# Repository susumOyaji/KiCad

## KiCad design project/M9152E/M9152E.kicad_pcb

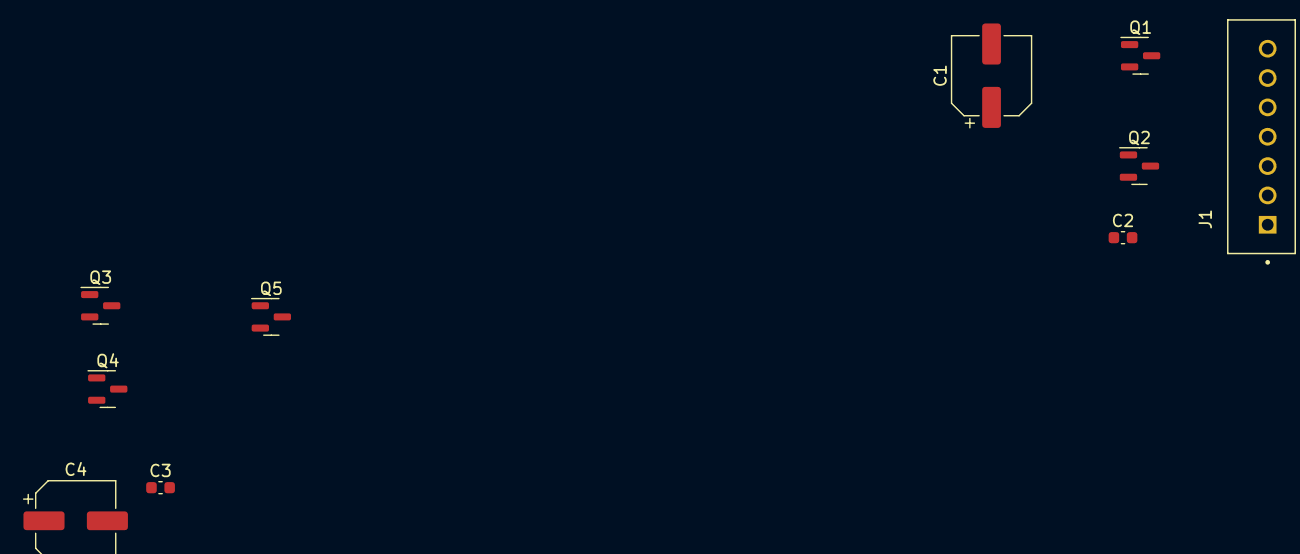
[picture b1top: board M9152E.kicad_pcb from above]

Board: 2 copper layers, 10 parts (0 on the bottom side), 8 nets, no tracks yet.

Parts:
C1, C4: C_Polarized_US; CP_Elec_6.3x5.4_Nichicon
C2, C3: 102; C_0603_1608Metric
J1: B7B-XH-A(LF)(SN); JST_B7B-XH-A(LF)(SN)
Q1, Q3: 2SC1815; SOT-23
Q2, Q4, Q5: 2SA1015; SOT-23

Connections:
GND: C2.2, Q2.2 (C), Q4.2 (C)
unnamed: C1.1, J1.5
unnamed: C1.2, Q1.1 (E), Q2.1 (E)
unnamed: C4.1, J1.4
unnamed: J1.7, Q1.2 (C), Q3.2 (C)
unnamed: Q1.3 (B), Q2.3 (B)
unnamed: C4.2, Q3.1 (E), Q4.1 (E)
unnamed: Q3.3 (B), Q4.3 (B)

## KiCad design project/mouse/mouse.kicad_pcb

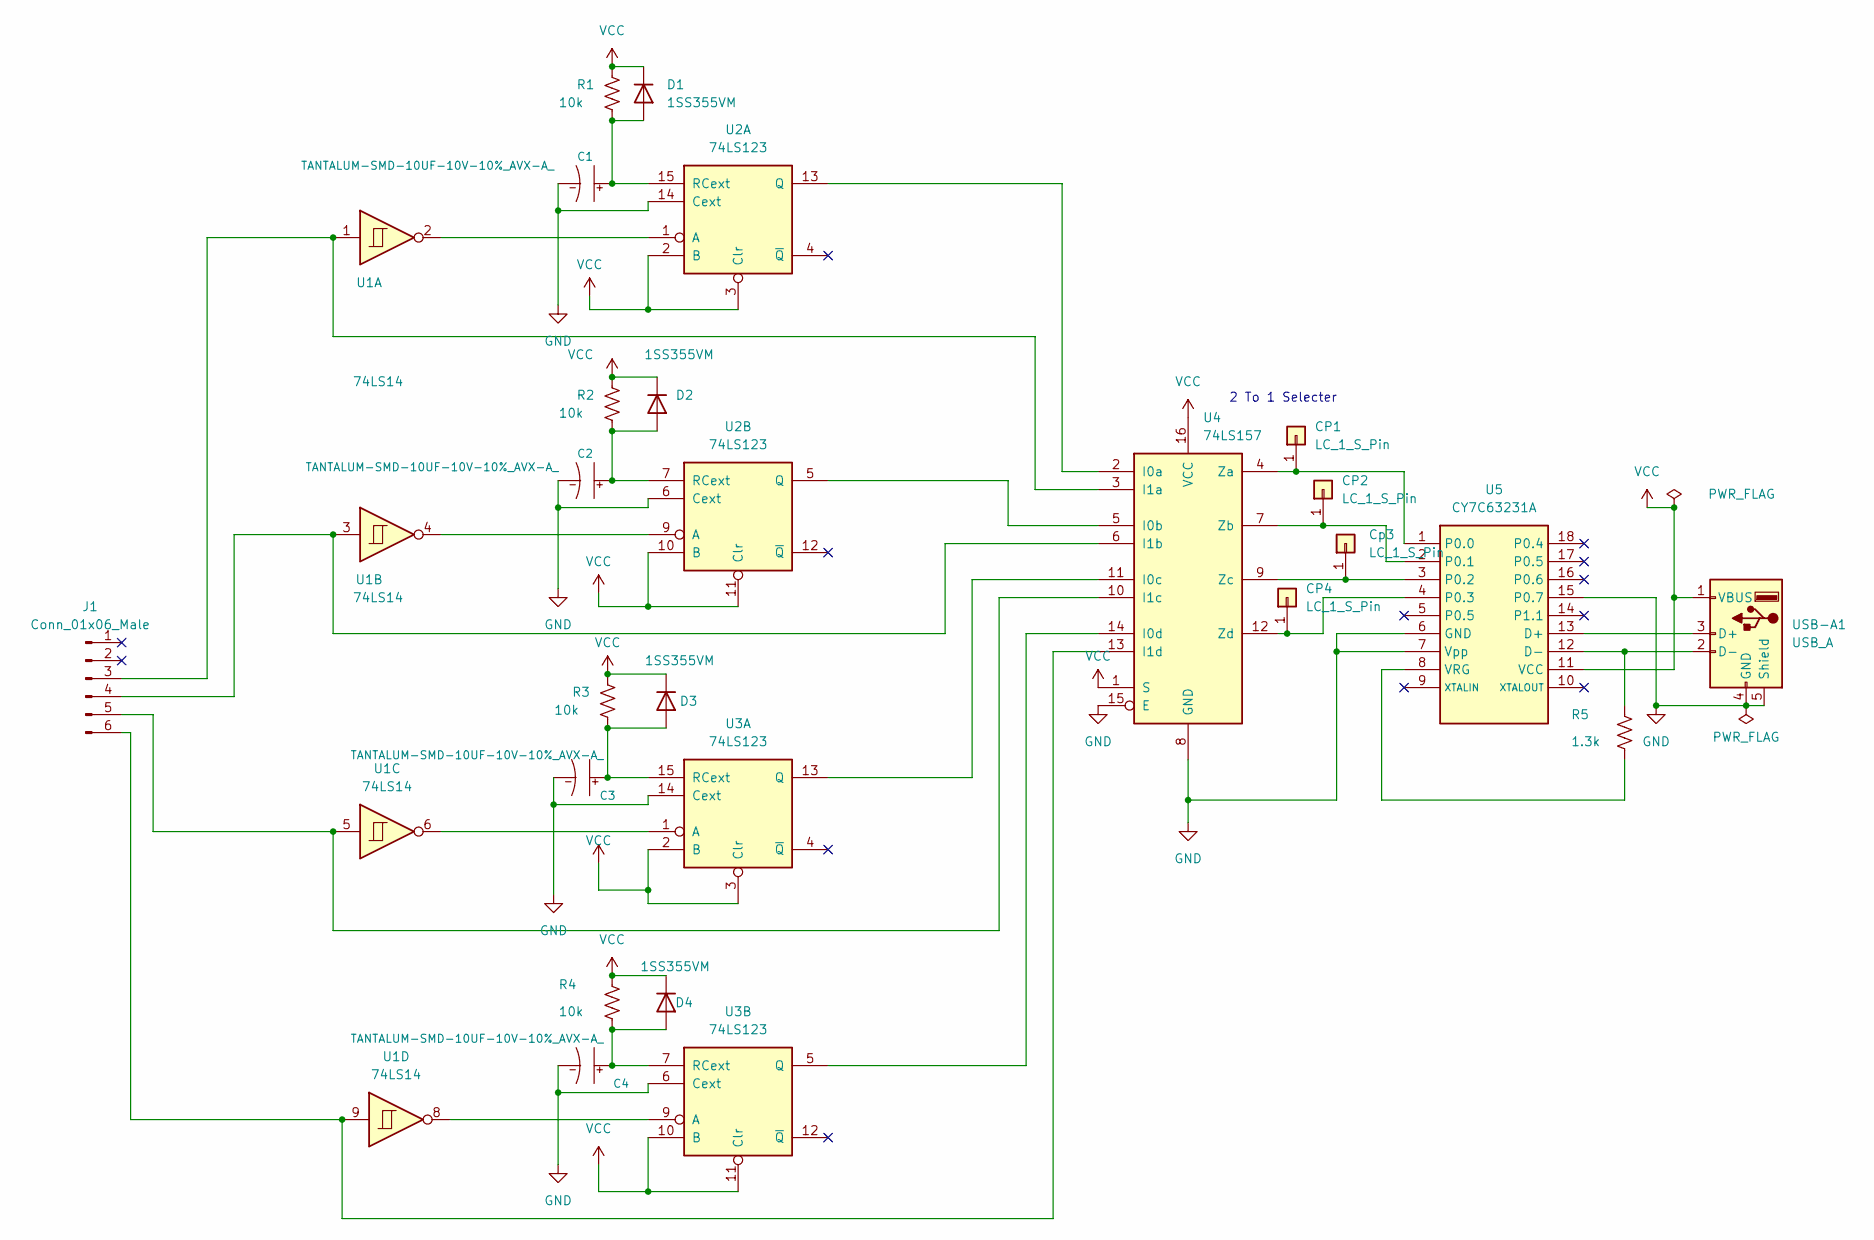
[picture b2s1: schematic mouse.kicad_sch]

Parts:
C1, C2, C3, C4: TANTALUM-SMD-10UF-10V-10%_AVX-A_; CP_Elec_3x5.3; MPN TAJA106K010RNJ
CP1, CP2, CP4: LC_1_S_Pin; CheckPin_1Pinp
Cp3: LC_1_S_Pin; CheckPin_1Pinp
D1, D2, D3, D4: 1SS355VM; D_DO-34_SOD68_P7.62mm_Horizontal
J1: Conn_01x06_Male; IL-6P-S3FP2-11
R1, R2, R3, R4: 10k; R_Axial_DIN0207_L6.3mm_D2.5mm_P10.16mm_Horizontal
R5: 1.3k; R_0603_1608Metric
U1: 74LS14; SOIC-14W_7.5x9mm_P1.27mm
U2, U3: 74LS123; SN74LS123NSR
U4: 74LS157; SOIC-16W_7.5x10.3mm_P1.27mm
U5: CY7C63231A; SOIC-18W_7.5x11.6mm_P1.27mm
USB-A1: USB_A; USB_A_CNCTech_1001-011-01101_Horizontal

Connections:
GND: C1.2 (-), C2.2 (-), C3.2 (-), C4.2 (-), U2.6 (Cext), U2.14 (Cext), U3.6 (Cext), U3.14 (Cext), U4.8 (GND), U4.15 (E), U5.6 (GND), U5.7 (Vpp), U5.15 (P0.7), USB-A1.4 (GND), USB-A1.5 (Shield); also elsewhere on the board
unnamed: C1.1 (+), D1.2 (A), R1.2, U2.15 (RCext)
unnamed: C2.1 (+), D2.2 (A), R2.2, U2.7 (RCext)
unnamed: C3.1 (+), D3.2 (A), R3.2, U3.15 (RCext)
unnamed: C4.1 (+), D4.2 (A), R4.2, U3.7 (RCext)
unnamed: CP1.1, U4.4 (Za), U5.1 (P0.0)
unnamed: CP2.1, U4.7 (Zb), U5.2 (P0.1)
unnamed: CP4.1, U4.12 (Zd), U5.4 (P0.3)
unnamed: Cp3.1, U4.9 (Zc), U5.3 (P0.2)
unnamed: J1.3, U1.1, U4.3 (I1a)
unnamed: R5.1, U5.12 (D-), USB-A1.2 (D-)
unnamed: R5.2, U5.8 (VRG)
unnamed: U1.2, U2.1 (A)
unnamed: J1.4, U1.3, U4.6 (I1b)
unnamed: U1.4, U2.9 (A)
unnamed: J1.5, U1.5, U4.10 (I1c)
unnamed: U1.6, U3.1 (A)
unnamed: U1.8, U3.9 (A)
unnamed: J1.6, U1.9, U4.13 (I1d)
unnamed: U2.5 (Q), U4.5 (I0b)
unnamed: U2.13 (Q), U4.2 (I0a)
unnamed: U3.5 (Q), U4.14 (I0d)
unnamed: U3.13 (Q), U4.11 (I0c)
unnamed: U5.13 (D+), USB-A1.3 (D+)
VCC: D1.1 (K), D2.1 (K), D3.1 (K), D4.1 (K), R1.1, R2.1, R3.1, R4.1, U2.2 (B), U2.3 (Clr), U2.10 (B), U2.11 (Clr), U3.2 (B), U3.3 (Clr), U3.10 (B), U3.11 (Clr), U4.1 (S), U4.16 (VCC), U5.11 (VCC), USB-A1.1 (VBUS)

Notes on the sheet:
2 To 1 Selecter

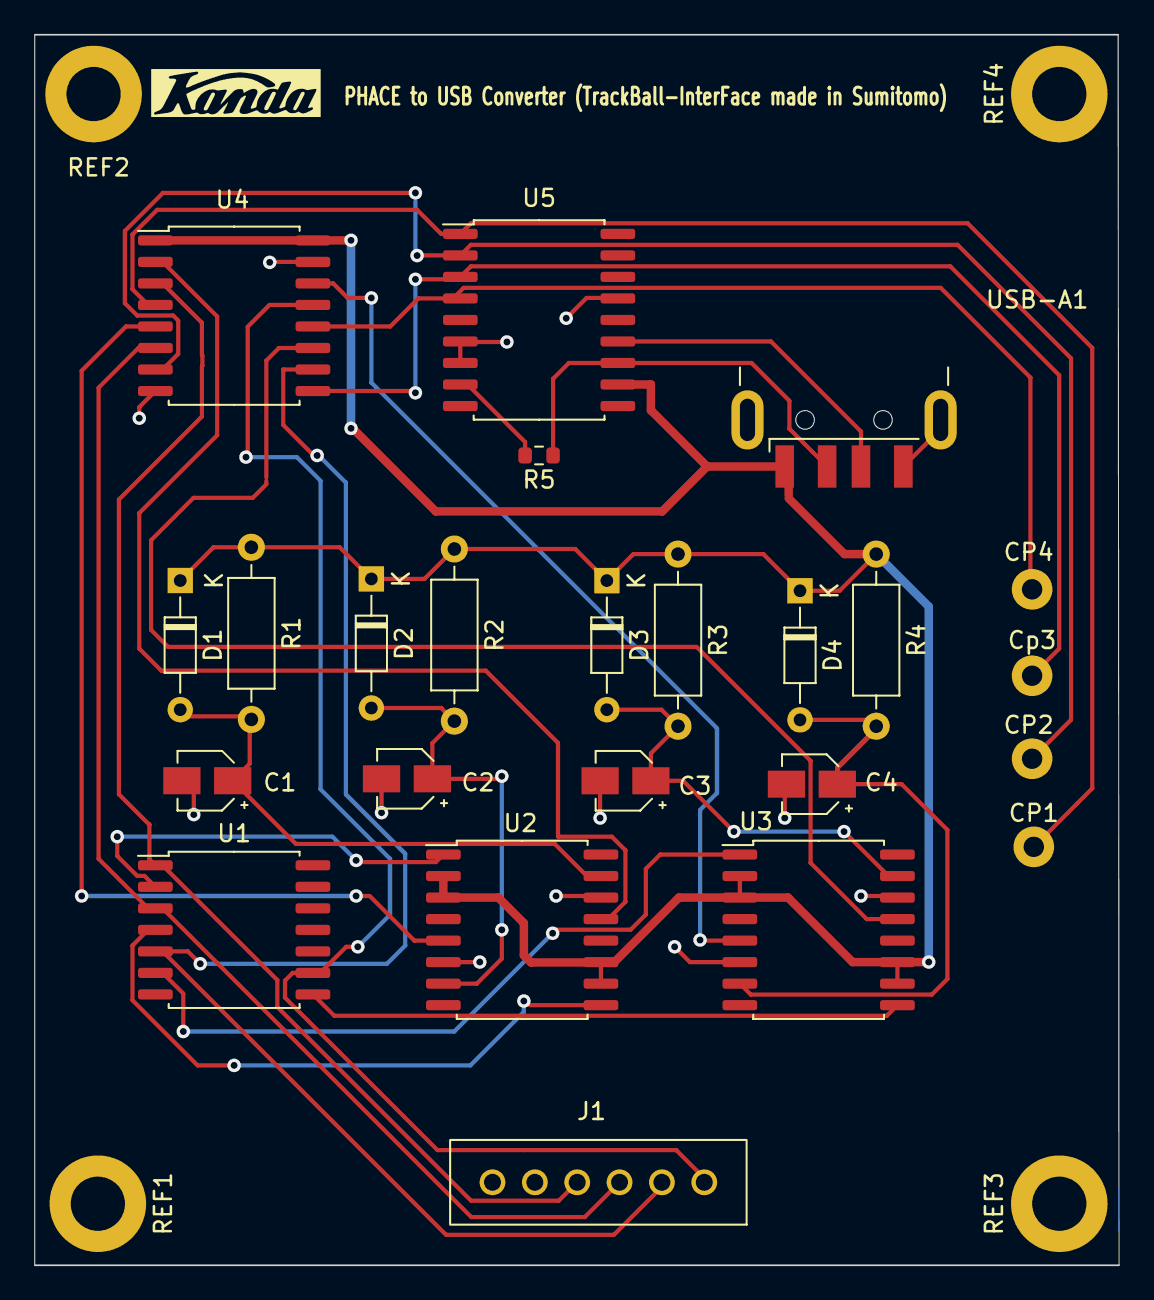
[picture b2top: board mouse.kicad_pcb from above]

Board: 2 copper layers, 64.0 x 72.6 mm, 28 parts (0 on the bottom side), 25 nets.

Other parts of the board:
REF1, REF2, REF3, REF4: MountingHole_3.2mm_M3_ISO7380_Pad

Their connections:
GND: REF1.1, REF2.1, REF3.1, REF4.1; also elsewhere on the board
